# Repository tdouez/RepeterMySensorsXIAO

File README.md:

//--------------------------------------------------------------------
//   __|              _/           _ )  |
//   _| |  |   ` \    -_)   -_)    _ \  |   -_)  |  |   -_)
//  _| \_,_| _|_|_| \___| \___|   ___/ _| \___| \_,_| \___|
//--------------------------------------------------------------------
# RepeterMySensorsXIAO

Répéter MySensors XIAO

Projet utilisant un XIAO Seeeduino et un module NRF24L01Ò

- Description disponible sur http://fumeebleue.fr

------------------------------------------------------------------------------------
Code mise à disposition selon les termes de la Licence Creative Commons Attribution
Pas d’Utilisation Commerciale.
Partage dans les Mêmes Conditions 4.0 International.
------------------------------------------------------------------------------------

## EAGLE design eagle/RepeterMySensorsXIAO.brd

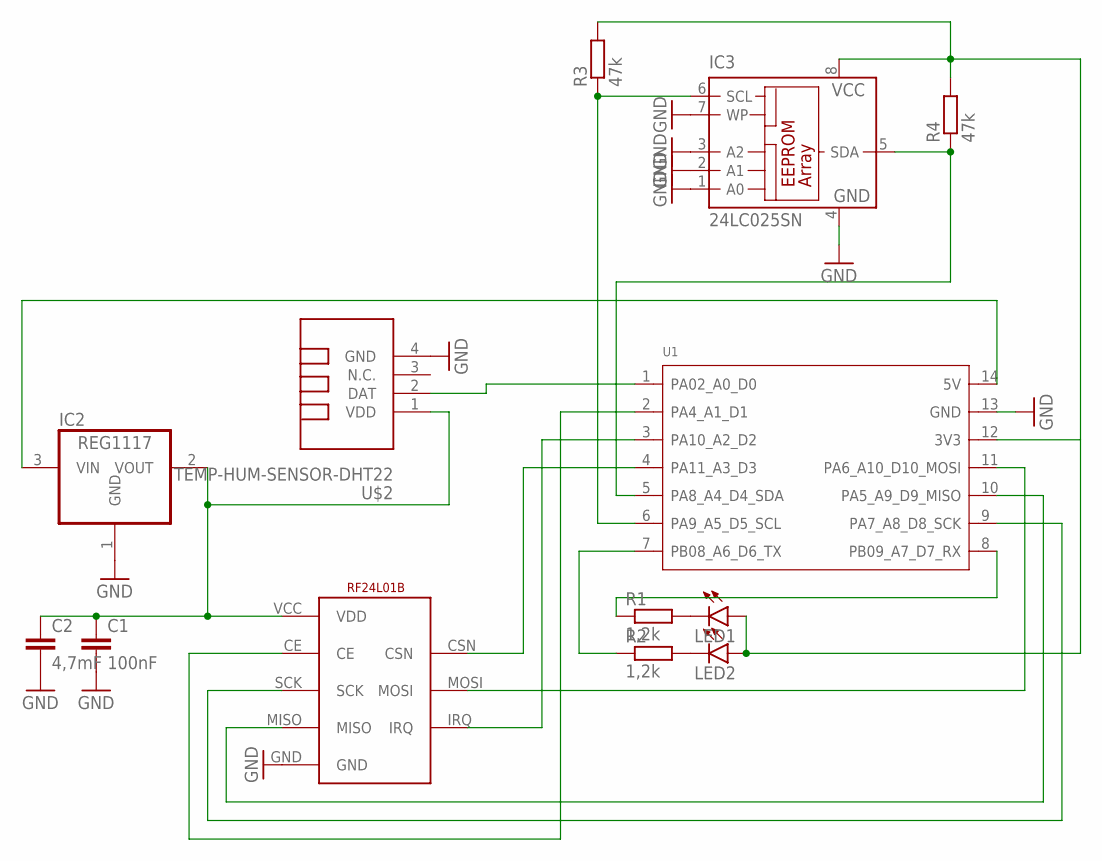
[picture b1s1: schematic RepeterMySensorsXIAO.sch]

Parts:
C1: 100nF; C1206
C2: 4,7mF; C1210
IC2: REG1117; SOT223
IC3: 24LC025SN; SO-08
LED1, LED2: LEDB152; Q62902-B152
R1, R2: 1,2k; M1206
R3, R4: 47k; M1206
U1: MOUDLE-SEEEDUINO-XIAO; MOUDLE14P-2.54-21X17.8MM
U$2: TEMP-HUM-SENSOR-DHT22
U$3: NRF24L01EBYTE; 24L01EBYTE

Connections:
GND: C1.2, C2.2, IC2.1 (GND), IC3.1 (A0), IC3.2 (A1), IC3.3 (A2), IC3.4 (GND), IC3.7 (WP), U1.13 (GND), U$2.4 (GND), U$3.GND
unnamed: C1.1, C2.1, IC2.2 (VOUT), U$2.1 (VDD), U$3.VCC (VDD)
unnamed: U1.11 (PA6_A10_D10_MOSI), U$3.MOSI
unnamed: IC3.8 (VCC), LED1.A, LED2.A, R3.2, R4.2, U1.12 (3V3)
unnamed: IC2.3 (VIN), U1.14 (5V)
unnamed: LED1.K (C), R1.2
unnamed: U1.3 (PA10_A2_D2), U$3.IRQ
unnamed: U1.4 (PA11_A3_D3), U$3.CSN
unnamed: U1.1 (PA02_A0_D0), U$2.2 (DAT)
unnamed: U1.10 (PA5_A9_D9_MISO), U$3.MISO
unnamed: U1.9 (PA7_A8_D8_SCK), U$3.SCK
unnamed: LED2.K (C), R2.2
unnamed: U1.2 (PA4_A1_D1), U$3.CE
unnamed: R2.1, U1.7 (PB08_A6_D6_TX)
unnamed: IC3.5 (SDA), R4.1, U1.5 (PA8_A4_D4_SDA)
unnamed: IC3.6 (SCL), R3.1, U1.6 (PA9_A5_D5_SCL)
unnamed: R1.1, U1.8 (PB09_A7_D7_RX)

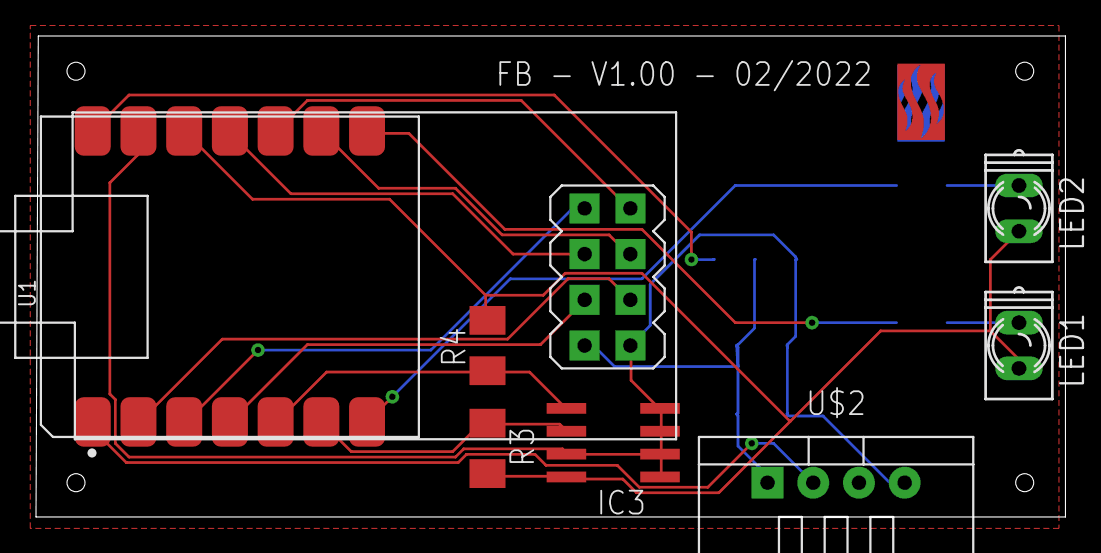
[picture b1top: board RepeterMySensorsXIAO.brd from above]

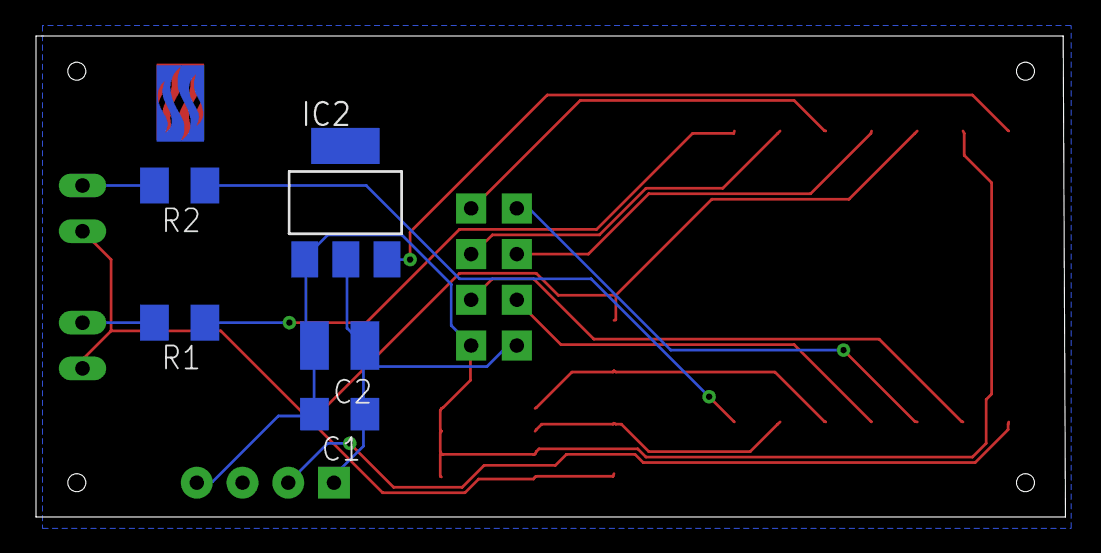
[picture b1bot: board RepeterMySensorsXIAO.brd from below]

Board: 2 copper layers, 57.2 x 26.7 mm, 15 parts (6 on the bottom side), 17 nets.

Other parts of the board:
U$1, U$4: FB

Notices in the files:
parts and their libraries:
diy-modules: Released under the Creative Commons Attribution 4.0 International License: http://creativecommons.org/licenses/by/4.0
